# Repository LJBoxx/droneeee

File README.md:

# RP2350 Flight controller stack 

This repo contains the design files for a rp2350 based flight controller stack, with an [am32](https://wiki.am32.ca/development/Hardware-Design.html) based 4-in-1 modulable esc.
The esc part is split onto 3 boards : 
- top and bottoma board with logic and mosfet drivers (logic)
- middle with mosfets and power converters (powerstage)

This design allows for repairability, if you want to change the power board for a higher current one or if you have burnt it, just swap it out and solder a new board ! 

I also wanted to experiment with the newly supported rp2350 mcu on betaflight ! Madflight has an esc but I haven't seen any on a 30.5x30.5 "classic" format yet.

Thhe flight controller is quite simple and only has support for the essential to fly digital fpv with : 
- uart for elrs/radio transceiver 
- uart for video like openipc or dji
- uart for gps (additionnal too!)
- one spare i2c port (because there was room for it :v)
- power (9v 3a max, 5v 3a max and 3v3 200ma max **only use if necessary**)

Additionally, there are also some betaflight rgb headers and buzzer. Since it is an rp2350 with PIO, it should be easy to repurpose the i2c port for something else. The pinout is also similar to the madflight fc3 but not exactly the same, in /src/firmware/betaflight/picoflight/config.h you will find the exact files needed to build a firmware along precompiled binary 

At first i wanted to make an esc to work with Alice's flight controller but in the end, i started changing some parts like power converters, removing analog parts and tried to overall optimize the design. In the end it wasnt the same anymore. I also wanted to experiment with the rp2350 as no flight controller exist yet with it. One more thing was trying to make even more compact designs than before, high density layout is fun but also a pain lol.. 

## Renders :

## Schematics 

# BOM 
| Name     | Qty     | Price  | Link   | Note |
| -------- | ------- | ------ | ------ | ----- |
| Components | 1     | 110usd  | /src/bom_export_fc.xls |
| PCB      | 3x5pcs  | 5usd/ea | https://jlcpcb.com/ | order each board design individually to have discounts !|
| total         |         | 125usd |  |shipping included

# ZINEE !!

# Build 
(to be done after i assemble it myself but basically soldering)

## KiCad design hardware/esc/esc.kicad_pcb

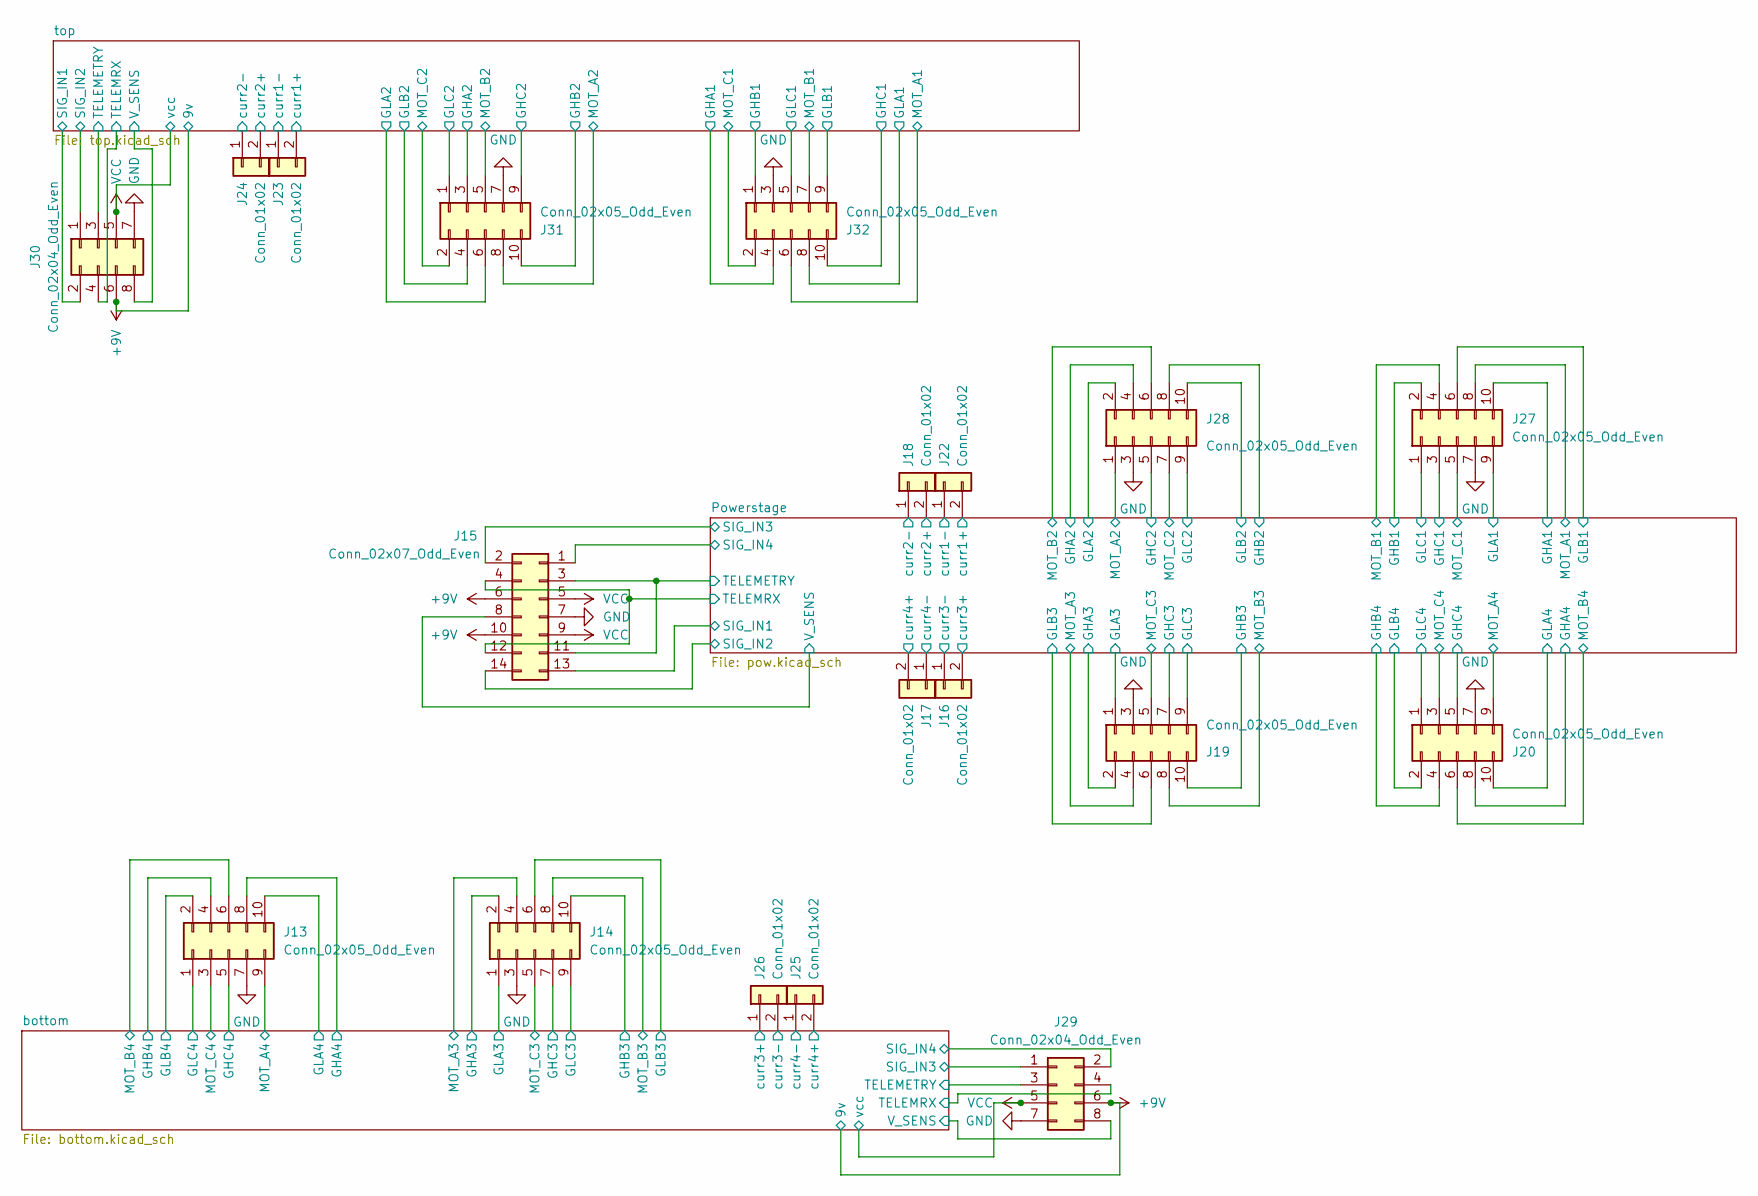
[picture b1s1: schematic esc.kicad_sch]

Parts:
J13, J14, J19, J20, J27, J28, J31, J32: Conn_02x05_Odd_Even; PinHeader_2x05_P1.00mm_Vertical; LCSC C22438182
J15: Conn_02x07_Odd_Even; PinHeader_2x07_P1.00mm_Vertical; LCSC x
J16, J17, J18, J22, J23, J24, J25, J26: Conn_01x02; PinHeader_1x02_P1.00mm_Vertical; LCSC C5138889
J29, J30: Conn_02x04_Odd_Even; PinHeader_2x04_P1.00mm_Vertical; LCSC x

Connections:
+9V: J15.6, J15.10, J29.6, J30.6; also elsewhere on the board
/Powerstage/GHA1: J27.10; also elsewhere on the board
/Powerstage/GHA2: J28.4; also elsewhere on the board
/Powerstage/GHA3: J19.2; also elsewhere on the board
/Powerstage/GHA4: J20.8; also elsewhere on the board
/Powerstage/GHB1: J27.2; also elsewhere on the board
/Powerstage/GHB2: J28.8; also elsewhere on the board
/Powerstage/GHB3: J19.10; also elsewhere on the board
/Powerstage/GHB4: J20.4; also elsewhere on the board
/Powerstage/GHC1: J27.3; also elsewhere on the board
/Powerstage/GHC2: J28.5; also elsewhere on the board
/Powerstage/GHC3: J19.7; also elsewhere on the board
/Powerstage/GHC4: J20.5; also elsewhere on the board
/Powerstage/GLA1: J27.9; also elsewhere on the board
/Powerstage/GLA2: J28.2; also elsewhere on the board
/Powerstage/GLA3: J19.1; also elsewhere on the board
/Powerstage/GLA4: J20.10; also elsewhere on the board
/Powerstage/GLB1: J27.6; also elsewhere on the board
/Powerstage/GLB2: J28.10; also elsewhere on the board
/Powerstage/GLB3: J19.6; also elsewhere on the board
/Powerstage/GLB4: J20.2; also elsewhere on the board
/Powerstage/GLC1: J27.1; also elsewhere on the board
/Powerstage/GLC2: J28.9; also elsewhere on the board
/Powerstage/GLC3: J19.9; also elsewhere on the board
/Powerstage/GLC4: J20.1; also elsewhere on the board
/Powerstage/MOT_A1: J27.8; also elsewhere on the board
/Powerstage/MOT_A2: J28.1; also elsewhere on the board
/Powerstage/MOT_A3: J19.4; also elsewhere on the board
/Powerstage/MOT_A4: J20.9; also elsewhere on the board
/Powerstage/MOT_B1: J27.4; also elsewhere on the board
/Powerstage/MOT_B2: J28.6; also elsewhere on the board
/Powerstage/MOT_B3: J19.8; also elsewhere on the board
/Powerstage/MOT_B4: J20.6; also elsewhere on the board
/Powerstage/MOT_C1: J27.5; also elsewhere on the board
/Powerstage/MOT_C2: J28.7; also elsewhere on the board
/Powerstage/MOT_C3: J19.5; also elsewhere on the board
/Powerstage/MOT_C4: J20.3; also elsewhere on the board
/Powerstage/SIG_IN1: J15.13; also elsewhere on the board
/Powerstage/SIG_IN2: J15.14; also elsewhere on the board
/Powerstage/SIG_IN3: J15.2; also elsewhere on the board
/Powerstage/SIG_IN4: J15.1; also elsewhere on the board
/Powerstage/TELEMETRY: J15.3, J15.11; also elsewhere on the board
/Powerstage/TELEMRX: J15.4, J15.12; also elsewhere on the board
/Powerstage/V_SENS: J15.8; also elsewhere on the board
/Powerstage/curr1+: J22.2; also elsewhere on the board
/Powerstage/curr1-: J22.1; also elsewhere on the board
/Powerstage/curr2+: J18.2; also elsewhere on the board
/Powerstage/curr2-: J18.1; also elsewhere on the board
/Powerstage/curr3+: J16.2; also elsewhere on the board
/Powerstage/curr3-: J16.1; also elsewhere on the board
/Powerstage/curr4+: J17.2; also elsewhere on the board
/Powerstage/curr4-: J17.1; also elsewhere on the board
/bottom/GHA3: J14.2; also elsewhere on the board
/bottom/GHA4: J13.8; also elsewhere on the board
/bottom/GHB3: J14.10; also elsewhere on the board
/bottom/GHB4: J13.4; also elsewhere on the board
/bottom/GHC3: J14.7; also elsewhere on the board
/bottom/GHC4: J13.5; also elsewhere on the board
/bottom/GLA3: J14.1; also elsewhere on the board
/bottom/GLA4: J13.10; also elsewhere on the board
/bottom/GLB3: J14.6; also elsewhere on the board
/bottom/GLB4: J13.2; also elsewhere on the board
/bottom/GLC3: J14.9; also elsewhere on the board
/bottom/GLC4: J13.1; also elsewhere on the board
/bottom/MOT_A3: J14.4; also elsewhere on the board
/bottom/MOT_A4: J13.9; also elsewhere on the board
/bottom/MOT_B3: J14.8; also elsewhere on the board
/bottom/MOT_B4: J13.6; also elsewhere on the board
/bottom/MOT_C3: J14.5; also elsewhere on the board
/bottom/MOT_C4: J13.3; also elsewhere on the board
/bottom/SIG_IN3: J29.1; also elsewhere on the board
/bottom/SIG_IN4: J29.2; also elsewhere on the board
/bottom/TELEMETRY: J29.3; also elsewhere on the board
/bottom/TELEMRX: J29.4; also elsewhere on the board
/bottom/V_SENS: J29.8; also elsewhere on the board
/bottom/curr3+: J26.1; also elsewhere on the board
/bottom/curr3-: J26.2; also elsewhere on the board
/bottom/curr4+: J25.2; also elsewhere on the board
/bottom/curr4-: J25.1; also elsewhere on the board
GND: J13.7, J14.3, J15.7, J19.3, J20.7, J27.7, J28.3, J29.7, J30.7, J31.7, J32.3; also elsewhere on the board
VCC: J15.5, J15.9, J29.5, J30.5; also elsewhere on the board

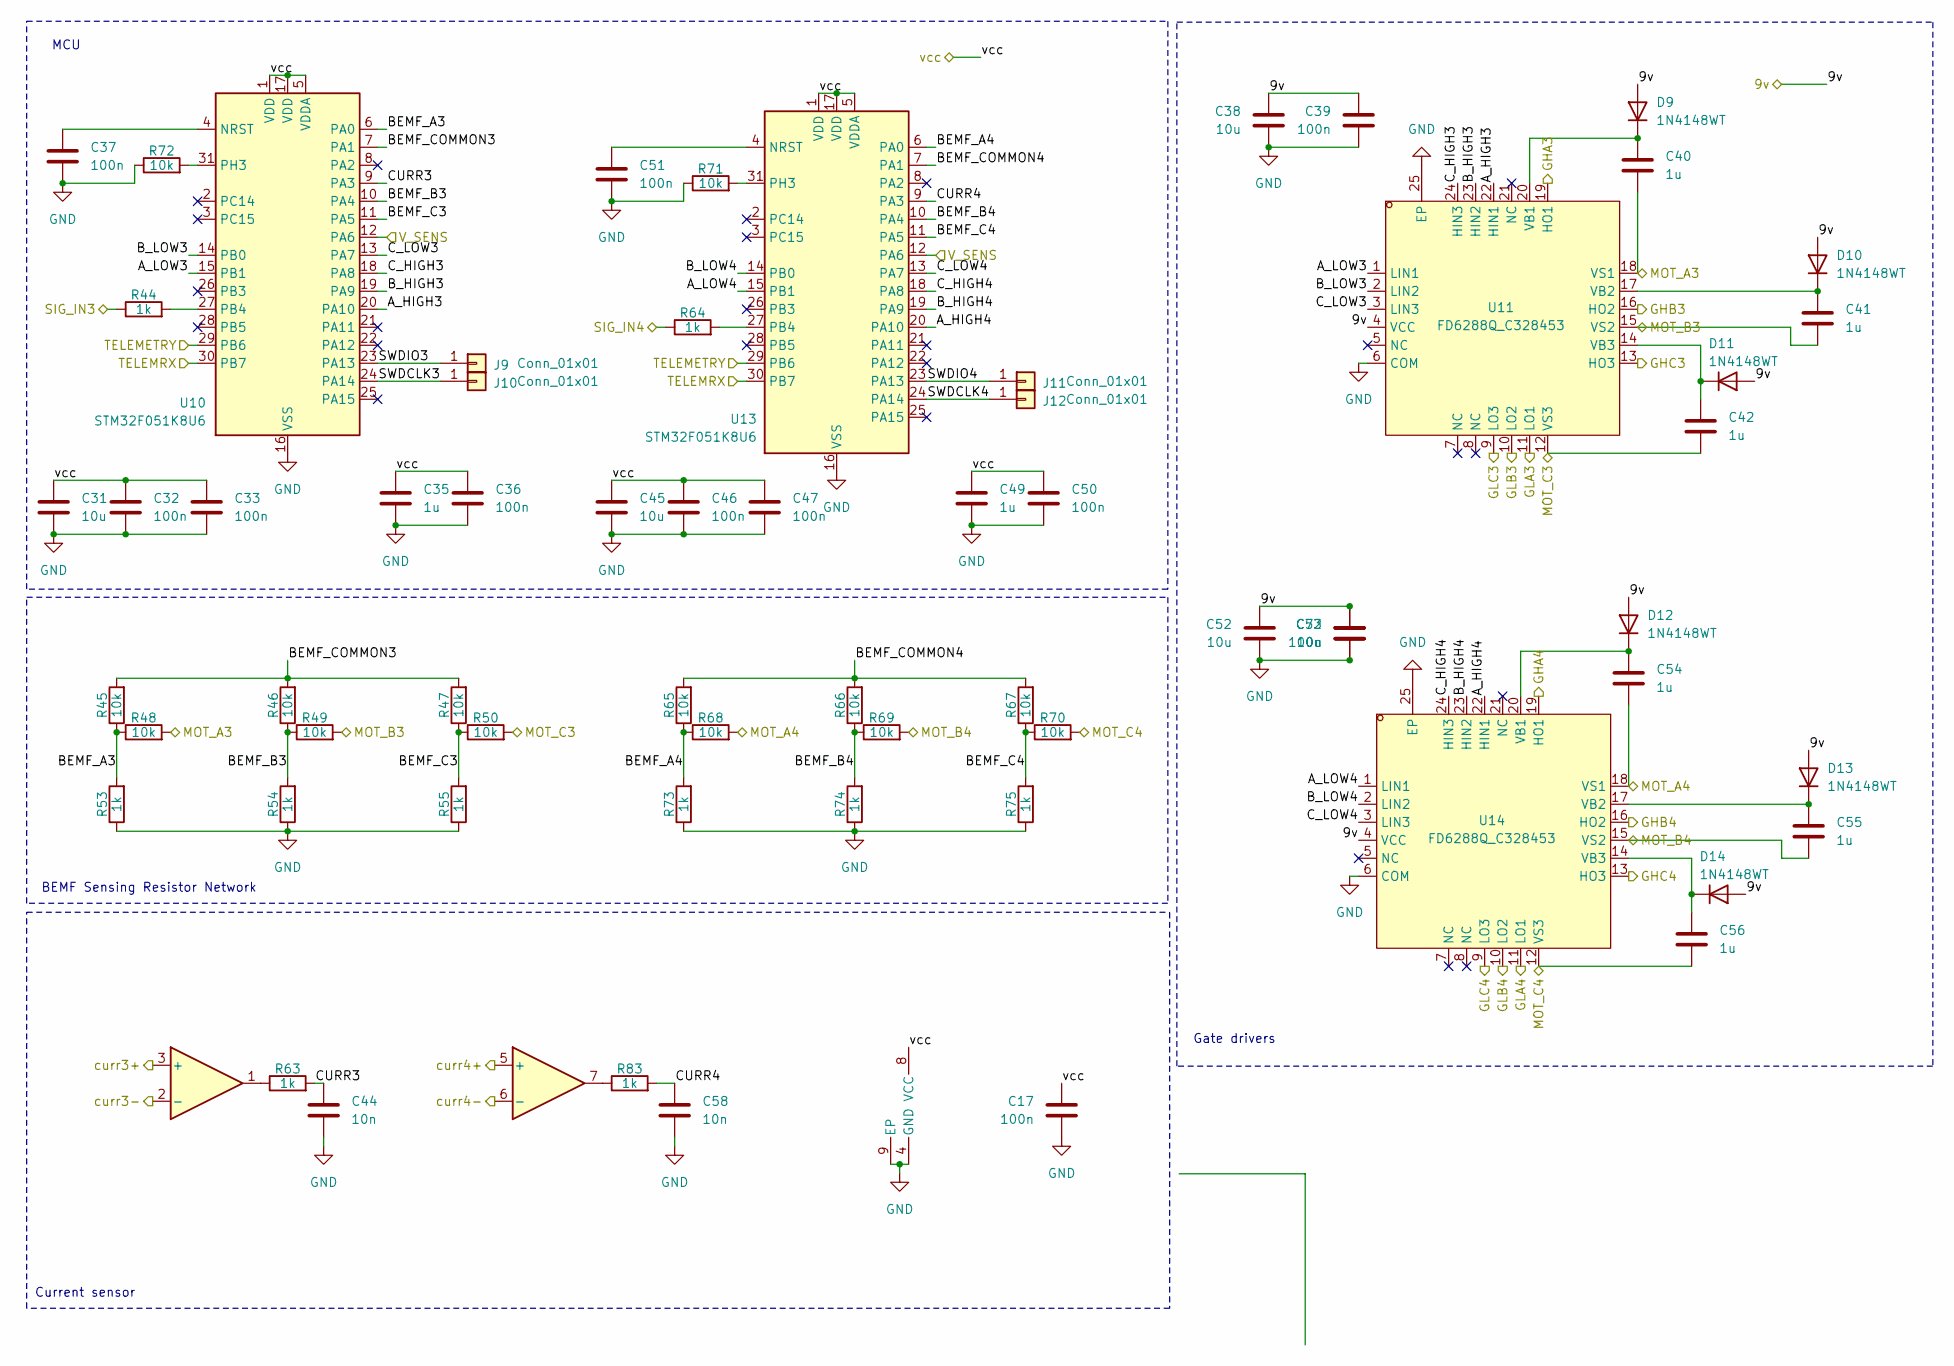
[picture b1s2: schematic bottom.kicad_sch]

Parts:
C17, C32, C33, C36, C37, C39, C46, C47, C50, C51, C53: 100n; C_0402_1005Metric; LCSC C1525
C31, C45: 10u; C_0805_2012Metric; LCSC C3039694
C35, C40, C41, C42, C49, C54, C55, C56: 1u; C_0603_1608Metric; LCSC C15849
C38, C52, C72: 10u; C_0603_1608Metric; LCSC C962136
C44, C58: 10n; C_0402_1005Metric; LCSC C15195
D9, D10, D11, D12, D13, D14: 1N4148WT; D_SOD-523; LCSC C917006
J9, J10, J11, J12: Conn_01x01; TestPoint_Pad_D1.0mm; LCSC x
R44, R53, R54, R55, R63, R64, R73, R74, R75, R83: 1k; R_0402_1005Metric; LCSC C445596
R45, R46, R47, R48, R49, R50, R65, R66, R67, R68, R69, R70, R71, R72: 10k; R_0402_1005Metric; LCSC C190095
U6: INA2180A1; WSON-8-1EP_2x2mm_P0.5mm_EP0.9x1.6mm; LCSC C2873353
U10, U13: STM32F051K8U6; QFN-32-1EP_5x5mm_P0.5mm_EP3.45x3.45mm; LCSC C72339
U11, U14: FD6288Q_C328453; QFN-24_L4.0-W4.0-P0.50-BL-EP2.6; LCSC Part C328453

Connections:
+9V: C38.1, C39.2, C52.1, C53.2, C72.1, D9.2 (A), D10.2 (A), D11.2 (A), D12.2 (A), D13.2 (A), D14.2 (A), U11.4 (VCC), U14.4 (VCC); also elsewhere on the board
/bottom/A_HIGH3: U10.20 (PA10), U11.22 (HIN1)
/bottom/A_HIGH4: U13.20 (PA10), U14.22 (HIN1)
/bottom/A_LOW3: U10.15 (PB1), U11.1 (LIN1)
/bottom/A_LOW4: U13.15 (PB1), U14.1 (LIN1)
/bottom/BEMF_A3: R45.1, R48.1, R53.2, U10.6 (PA0)
/bottom/BEMF_A4: R65.1, R68.1, R73.2, U13.6 (PA0)
/bottom/BEMF_B3: R46.1, R49.1, R54.2, U10.10 (PA4)
/bottom/BEMF_B4: R66.1, R69.1, R74.2, U13.10 (PA4)
/bottom/BEMF_C3: R47.1, R50.1, R55.2, U10.11 (PA5)
/bottom/BEMF_C4: R67.1, R70.1, R75.2, U13.11 (PA5)
/bottom/BEMF_COMMON3: R45.2, R46.2, R47.2, U10.7 (PA1)
/bottom/BEMF_COMMON4: R65.2, R66.2, R67.2, U13.7 (PA1)
/bottom/B_HIGH3: U10.19 (PA9), U11.23 (HIN2)
/bottom/B_HIGH4: U13.19 (PA9), U14.23 (HIN2)
/bottom/B_LOW3: U10.14 (PB0), U11.2 (LIN2)
/bottom/B_LOW4: U13.14 (PB0), U14.2 (LIN2)
/bottom/CURR3: C44.1, R63.2, U10.9 (PA3)
/bottom/CURR4: C58.1, R83.2, U13.9 (PA3)
/bottom/C_HIGH3: U10.18 (PA8), U11.24 (HIN3)
/bottom/C_HIGH4: U13.18 (PA8), U14.24 (HIN3)
/bottom/C_LOW3: U10.13 (PA7), U11.3 (LIN3)
/bottom/C_LOW4: U13.13 (PA7), U14.3 (LIN3)
/bottom/GHA3: U11.19 (HO1); also elsewhere on the board
/bottom/GHA4: U14.19 (HO1); also elsewhere on the board
/bottom/GHB3: U11.16 (HO2); also elsewhere on the board
/bottom/GHB4: U14.16 (HO2); also elsewhere on the board
/bottom/GHC3: U11.13 (HO3); also elsewhere on the board
/bottom/GHC4: U14.13 (HO3); also elsewhere on the board
/bottom/GLA3: U11.11 (LO1); also elsewhere on the board
/bottom/GLA4: U14.11 (LO1); also elsewhere on the board
/bottom/GLB3: U11.10 (LO2); also elsewhere on the board
/bottom/GLB4: U14.10 (LO2); also elsewhere on the board
/bottom/GLC3: U11.9 (LO3); also elsewhere on the board
/bottom/GLC4: U14.9 (LO3); also elsewhere on the board
/bottom/MOT_A3: C40.1, R48.2, U11.18 (VS1); also elsewhere on the board
/bottom/MOT_A4: C54.1, R68.2, U14.18 (VS1); also elsewhere on the board
/bottom/MOT_B3: C41.1, R49.2, U11.15 (VS2); also elsewhere on the board
/bottom/MOT_B4: C55.1, R69.2, U14.15 (VS2); also elsewhere on the board
/bottom/MOT_C3: C42.1, R50.2, U11.12 (VS3); also elsewhere on the board
/bottom/MOT_C4: C56.1, R70.2, U14.12 (VS3); also elsewhere on the board
/bottom/SIG_IN3: R44.1; also elsewhere on the board
/bottom/SIG_IN4: R64.1; also elsewhere on the board
/bottom/SWDCLK3: J10.1 (Pin_1_1), U10.24 (PA14)
/bottom/SWDCLK4: J12.1 (Pin_1_1), U13.24 (PA14)
/bottom/SWDIO3: J9.1 (Pin_1_1), U10.23 (PA13)
/bottom/SWDIO4: J11.1 (Pin_1_1), U13.23 (PA13)
/bottom/TELEMETRY: U10.29 (PB6), U13.29 (PB6); also elsewhere on the board
/bottom/TELEMRX: U10.30 (PB7), U13.30 (PB7); also elsewhere on the board
/bottom/V_SENS: U10.12 (PA6), U13.12 (PA6); also elsewhere on the board
/bottom/curr3+: U6.3 (+); also elsewhere on the board
/bottom/curr3-: U6.2 (-); also elsewhere on the board
/bottom/curr4+: U6.5 (+); also elsewhere on the board
/bottom/curr4-: U6.6 (-); also elsewhere on the board
GND: C17.2, C31.2, C32.2, C33.2, C35.2, C36.2, C37.2, C38.2, C39.1, C44.2, C45.2, C46.2, C47.2, C49.2, C50.2, C51.2, C52.2, C53.1, C58.2, C72.2, R53.1, R54.1, R55.1, R71.1, R72.1, R73.1, R74.1, R75.1, U6.4 (GND), U6.9 (EP), U10.16 (VSS), U10.32 (VSS), U10.33 (VSS), U11.6 (COM), U11.25 (EP), U13.16 (VSS), U13.32 (VSS), U13.33 (VSS), U14.6 (COM), U14.25 (EP); also elsewhere on the board
unnamed: C40.2, D9.1 (K), U11.20 (VB1)
unnamed: C41.2, D10.1 (K), U11.17 (VB2)
unnamed: C42.2, D11.1 (K), U11.14 (VB3)
unnamed: C54.2, D12.1 (K), U14.20 (VB1)
unnamed: C55.2, D13.1 (K), U14.17 (VB2)
unnamed: C56.2, D14.1 (K), U14.14 (VB3)
unnamed: R63.1, U6.1
unnamed: R83.1, U6.7
unnamed: C37.1, U10.4 (NRST)
unnamed: R44.2, U10.27 (PB4)
unnamed: R72.2, U10.31 (PH3)
unnamed: C51.1, U13.4 (NRST)
unnamed: R64.2, U13.27 (PB4)
unnamed: R71.2, U13.31 (PH3)
VCC: C17.1, C31.1, C32.1, C33.1, C35.1, C36.1, C45.1, C46.1, C47.1, C49.1, C50.1, U6.8 (VCC), U10.1 (VDD), U10.5 (VDDA), U10.17 (VDD), U13.1 (VDD), U13.5 (VDDA), U13.17 (VDD); also elsewhere on the board

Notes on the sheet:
Current sensor
BEMF Sensing Resistor Network
Gate drivers
MCU

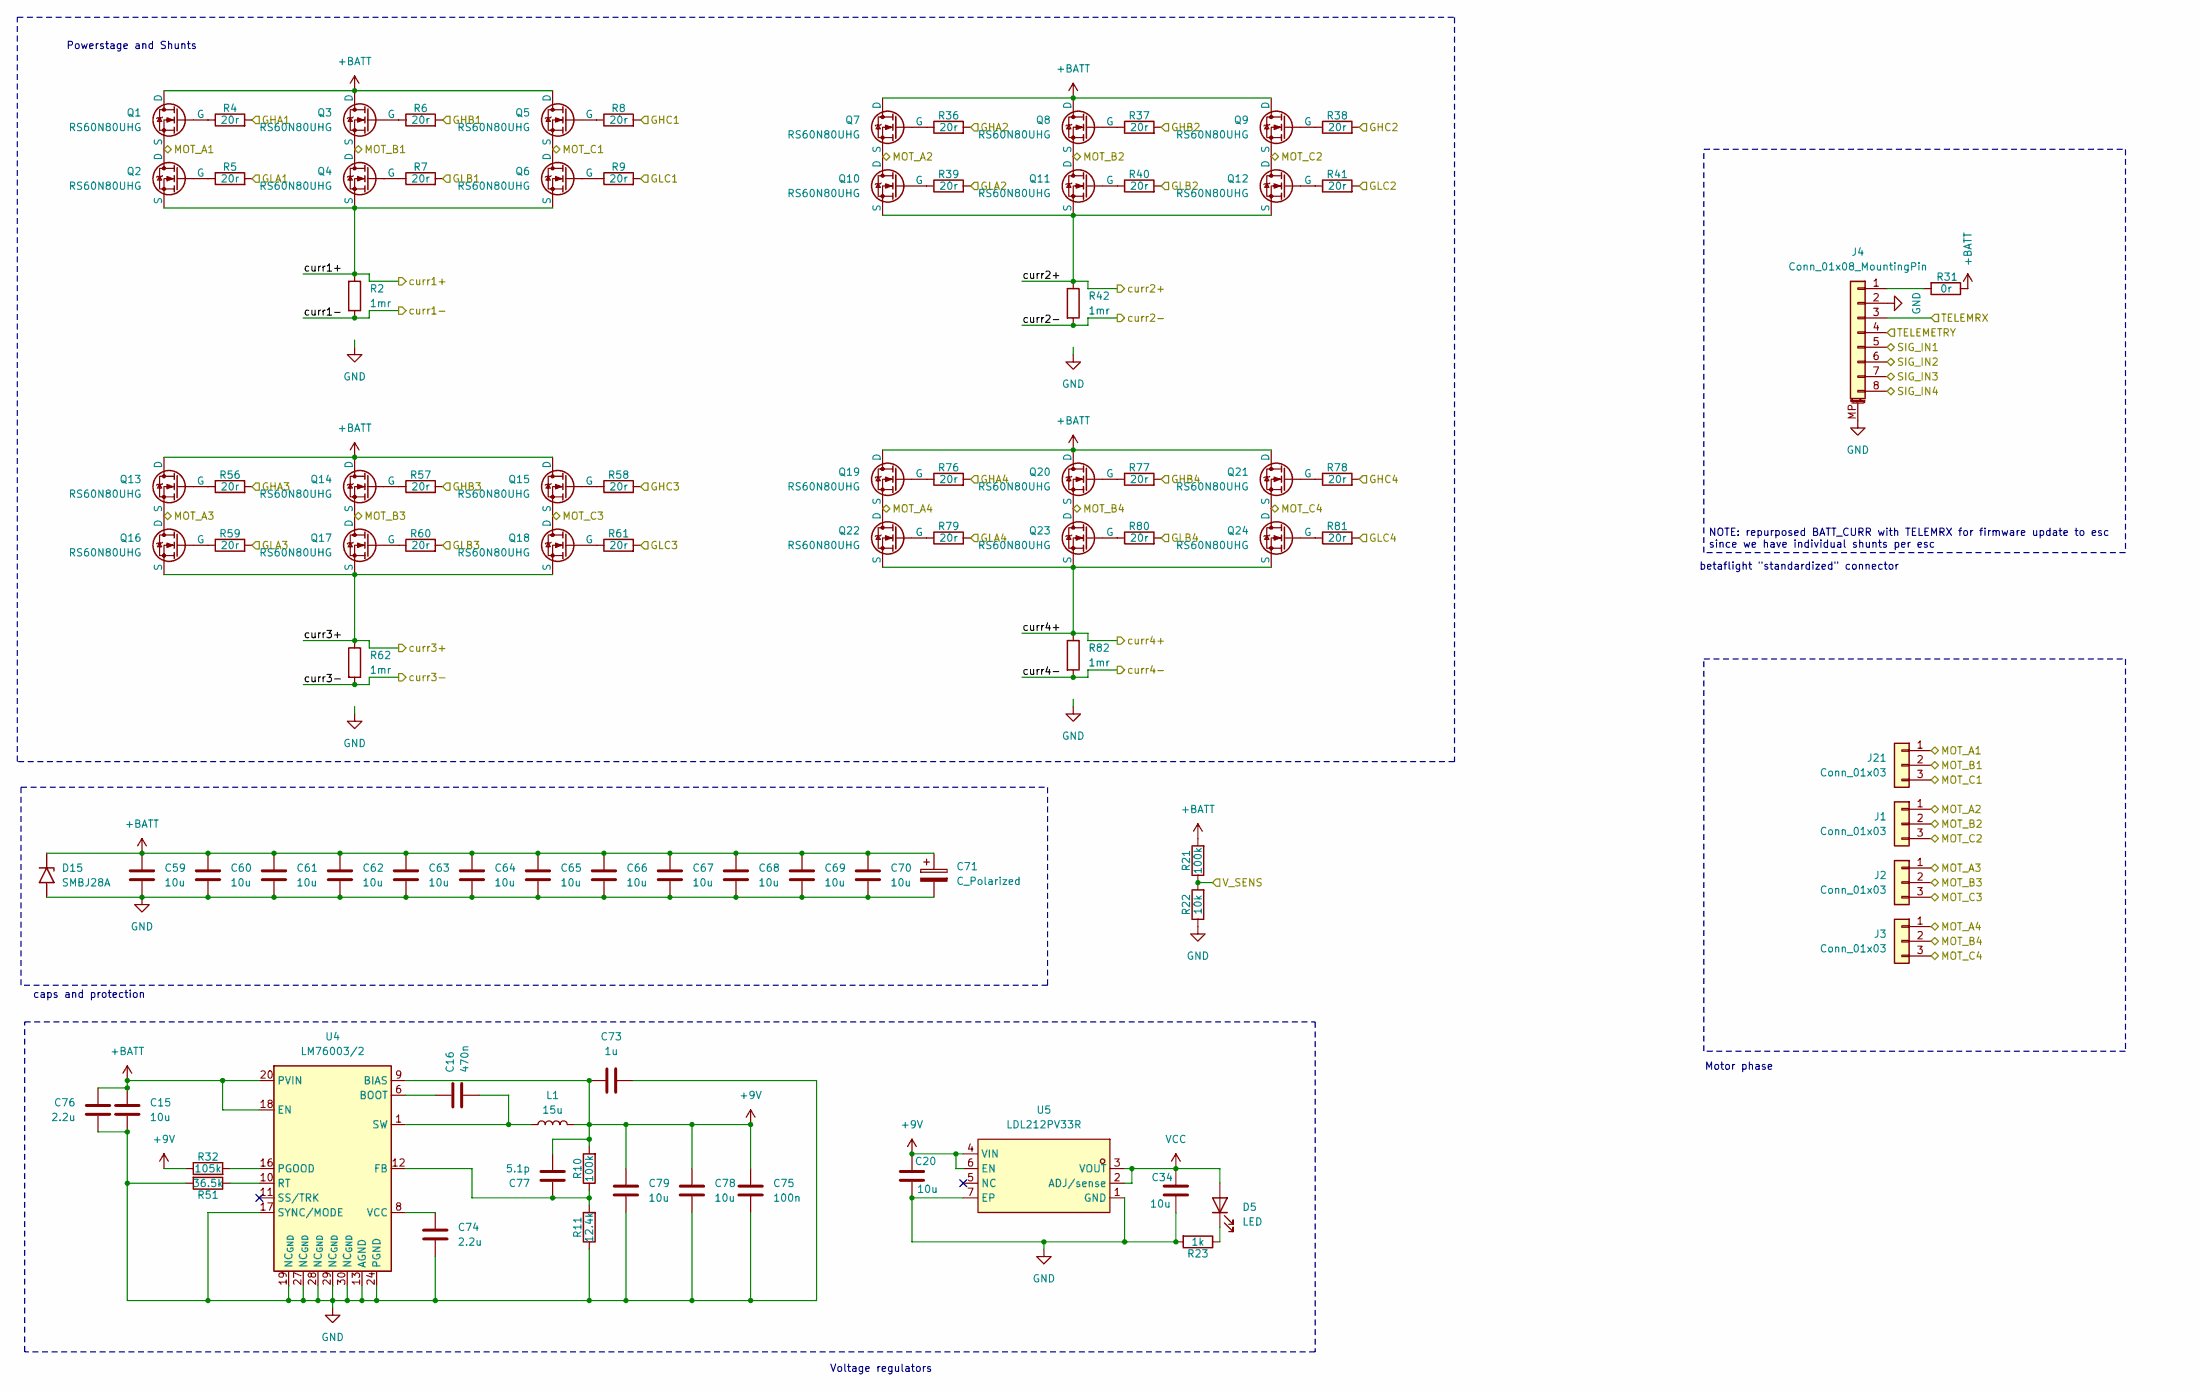
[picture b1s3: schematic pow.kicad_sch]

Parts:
C15, C20, C34, C59, C60, C61, C62, C63, C64, C65, C66, C67, C68, C69, C70, C78, C79: 10u; C_0805_2012Metric; LCSC C3039694
C16: 470n; C_0402_1005Metric; LCSC C92361
C71: C_Polarized; C_Disc_D5.0mm_W2.5mm_P5.00mm; LCSC x
C73: 1u; C_0402_1005Metric; LCSC C913556
C74: 2.2u; C_0402_1005Metric; LCSC C12530
C75: 100n; C_0402_1005Metric; LCSC C1525
C76: 2.2u; C_0603_1608Metric; LCSC C913904
C77: 5.1p; C_0402_1005Metric; LCSC C541354
D5: LED; D_0603_1608Metric; LCSC C7496819
D15: SMBJ28A; D_SMB; LCSC C178227
J1, J2, J3, J21: Conn_01x03; Phase_Pads; LCSC x
J4: Conn_01x08_MountingPin; JST_SH_SM08B-SRSS-TB_1x08-1MP_P1.00mm_Horizontal; LCSC Part C160407
L1: 15u; inductor FANGCHENG FC-ALX 5050D-150MT; LCSC C5370912
Q1, Q2, Q3, Q4, Q5, Q6, Q7, Q8, Q9, Q10, Q11, Q12, Q13, Q14, Q15, Q16, Q17, Q18, Q19, Q20, Q21, Q22, Q23, Q24: RS60N80UHG; DFN-8_L5.8-W4.9-P1.27-LS6.0-BL-1; LCSC C51904706
R2, R42, R62, R82: 1mr; R_1210_3225Metric; LCSC C4173351
R4, R5, R6, R7, R8, R9, R36, R37, R38, R39, R40, R41, R56, R57, R58, R59, R60, R61, R76, R77, R78, R79, R80, R81: 20r; R_0402_1005Metric; LCSC C2909334
R10, R21: 100k; R_0402_1005Metric; LCSC C445619
R11: 12.4k; R_0402_1005Metric; LCSC C490814
R22: 10k; R_0402_1005Metric; LCSC C190095
R23: 1k; R_0402_1005Metric; LCSC C445596
R31: 0r; R_0402_1005Metric; LCSC x(shunt)
R32: 105k; R_0402_1005Metric; LCSC C2933067
R51: 36.5k; R_0402_1005Metric; LCSC C42396638
U4: LM76003/2; Texas_RNP0030B_WQFN-30-1EP_4x6mm_P0.5mm_EP1.8x4.5mm_Thermal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; LCSC C470958
U5: LDL212PV33R; DFN-6_L2.0-W2.0-P0.50-BL-EP1.45; MPN LDL212PV33R; LCSC Part C2969892

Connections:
+9V: C20.1, C73.1, C75.1, C77.2, C78.1, C79.1, L1.2, R10.2, R32.1, U4.9 (BIAS), U5.4 (VIN), U5.6 (EN); also elsewhere on the board
+BATT: C15.1, C59.1, C60.1, C61.1, C62.1, C63.1, C64.1, C65.1, C66.1, C67.1, C68.1, C69.1, C70.1, C71.1, C76.1, D15.1 (A1), Q1.D, Q3.D, Q5.D, Q7.D, Q8.D, Q9.D, Q13.D, Q14.D, Q15.D, Q19.D, Q20.D, Q21.D, R21.2, R31.1, U4.18 (EN), U4.20 (PVIN), U4.21 (PVIN), U4.22 (PVIN)
/Powerstage/GHA1: R4.2; also elsewhere on the board
/Powerstage/GHA2: R36.2; also elsewhere on the board
/Powerstage/GHA3: R56.2; also elsewhere on the board
/Powerstage/GHA4: R76.2; also elsewhere on the board
/Powerstage/GHB1: R6.2; also elsewhere on the board
/Powerstage/GHB2: R37.2; also elsewhere on the board
/Powerstage/GHB3: R57.2; also elsewhere on the board
/Powerstage/GHB4: R77.2; also elsewhere on the board
/Powerstage/GHC1: R8.2; also elsewhere on the board
/Powerstage/GHC2: R38.2; also elsewhere on the board
/Powerstage/GHC3: R58.2; also elsewhere on the board
/Powerstage/GHC4: R78.2; also elsewhere on the board
/Powerstage/GLA1: R5.2; also elsewhere on the board
/Powerstage/GLA2: R39.2; also elsewhere on the board
/Powerstage/GLA3: R59.2; also elsewhere on the board
/Powerstage/GLA4: R79.2; also elsewhere on the board
/Powerstage/GLB1: R7.2; also elsewhere on the board
/Powerstage/GLB2: R40.2; also elsewhere on the board
/Powerstage/GLB3: R60.2; also elsewhere on the board
/Powerstage/GLB4: R80.2; also elsewhere on the board
/Powerstage/GLC1: R9.2; also elsewhere on the board
/Powerstage/GLC2: R41.2; also elsewhere on the board
/Powerstage/GLC3: R61.2; also elsewhere on the board
/Powerstage/GLC4: R81.2; also elsewhere on the board
/Powerstage/MOT_A1: J21.1, Q1.S, Q2.D; also elsewhere on the board
/Powerstage/MOT_A2: J1.1, Q7.S, Q10.D; also elsewhere on the board
/Powerstage/MOT_A3: J2.1, Q13.S, Q16.D; also elsewhere on the board
/Powerstage/MOT_A4: J3.1, Q19.S, Q22.D; also elsewhere on the board
/Powerstage/MOT_B1: J21.2, Q3.S, Q4.D; also elsewhere on the board
/Powerstage/MOT_B2: J1.2, Q8.S, Q11.D; also elsewhere on the board
/Powerstage/MOT_B3: J2.2, Q14.S, Q17.D; also elsewhere on the board
/Powerstage/MOT_B4: J3.2, Q20.S, Q23.D; also elsewhere on the board
/Powerstage/MOT_C1: J21.3, Q5.S, Q6.D; also elsewhere on the board
/Powerstage/MOT_C2: J1.3, Q9.S, Q12.D; also elsewhere on the board
/Powerstage/MOT_C3: J2.3, Q15.S, Q18.D; also elsewhere on the board
/Powerstage/MOT_C4: J3.3, Q21.S, Q24.D; also elsewhere on the board
/Powerstage/SIG_IN1: J4.5; also elsewhere on the board
/Powerstage/SIG_IN2: J4.6; also elsewhere on the board
/Powerstage/SIG_IN3: J4.7; also elsewhere on the board
/Powerstage/SIG_IN4: J4.8; also elsewhere on the board
/Powerstage/TELEMETRY: J4.4; also elsewhere on the board
/Powerstage/TELEMRX: J4.3; also elsewhere on the board
/Powerstage/V_SENS: R21.1, R22.2; also elsewhere on the board
/Powerstage/curr1+: Q2.S, Q4.S, Q6.S, R2.1; also elsewhere on the board
/Powerstage/curr1-: R2.2; also elsewhere on the board
/Powerstage/curr2+: Q10.S, Q11.S, Q12.S, R42.1; also elsewhere on the board
/Powerstage/curr2-: R42.2; also elsewhere on the board
/Powerstage/curr3+: Q16.S, Q17.S, Q18.S, R62.1; also elsewhere on the board
/Powerstage/curr3-: R62.2; also elsewhere on the board
/Powerstage/curr4+: Q22.S, Q23.S, Q24.S, R82.1; also elsewhere on the board
/Powerstage/curr4-: R82.2; also elsewhere on the board
GND: C15.2, C20.2, C34.2, C59.2, C60.2, C61.2, C62.2, C63.2, C64.2, C65.2, C66.2, C67.2, C68.2, C69.2, C70.2, C71.2, C73.2, C74.2, C75.2, C76.2, C78.2, C79.2, D15.2 (A2), J4.2, J4.MP (MountPin), R11.1, R22.1, R23.2, R51.2, U4.13 (AGND), U4.14 (AGND), U4.15 (AGND), U4.17 (SYNC/MODE), U4.19 (NC_{GND}), U4.24 (PGND), U4.25 (PGND), U4.26 (PGND), U4.27 (NC_{GND}), U4.28 (NC_{GND}), U4.29 (NC_{GND}), U4.30 (NC_{GND}), U4.31 (AGND), U5.1 (GND), U5.7 (EP); also elsewhere on the board
unnamed: C16.2, L1.1, U4.1 (SW), U4.2 (SW), U4.3 (SW), U4.4 (SW), U4.5 (SW)
unnamed: D5.1 (K), R23.1
unnamed: J4.1, R31.2
unnamed: Q1.G, R4.1
unnamed: Q2.G, R5.1
unnamed: Q3.G, R6.1
unnamed: Q4.G, R7.1
unnamed: Q5.G, R8.1
unnamed: Q6.G, R9.1
unnamed: Q7.G, R36.1
unnamed: Q8.G, R37.1
unnamed: Q9.G, R38.1
unnamed: Q10.G, R39.1
unnamed: Q11.G, R40.1
unnamed: Q12.G, R41.1
unnamed: Q13.G, R56.1
unnamed: Q14.G, R57.1
unnamed: Q15.G, R58.1
unnamed: Q16.G, R59.1
unnamed: Q17.G, R60.1
unnamed: Q18.G, R61.1
unnamed: Q19.G, R76.1
unnamed: Q20.G, R77.1
unnamed: Q21.G, R78.1
unnamed: Q22.G, R79.1
unnamed: Q23.G, R80.1
unnamed: Q24.G, R81.1
unnamed: C16.1, U4.6 (BOOT)
unnamed: C77.1, R10.1, R11.2, U4.12 (FB)
unnamed: R32.2, U4.16 (PGOOD)
unnamed: R51.1, U4.10 (RT)
unnamed: C74.1, U4.8 (VCC)
VCC: C34.1, D5.2 (A), U5.2 (ADJ/sense), U5.3 (VOUT); also elsewhere on the board

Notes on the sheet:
NOTE: repurposed BATT_CURR with TELEMRX for firmware update to esc since we have individual shunts per esc
caps and protection
Powerstage and Shunts
betaflight "standardized" connector
Voltage regulators
Motor phase

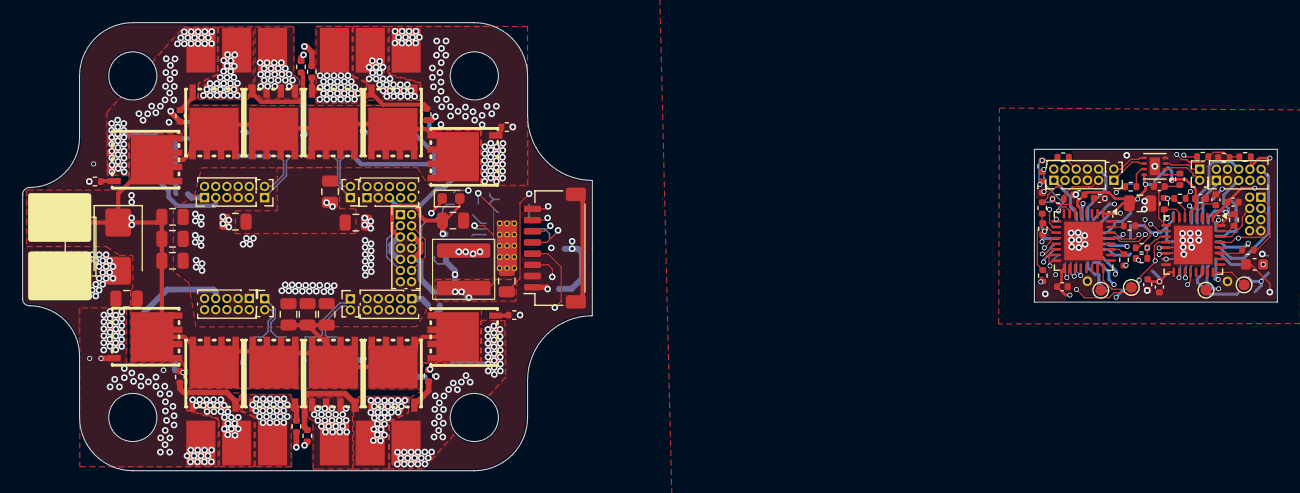
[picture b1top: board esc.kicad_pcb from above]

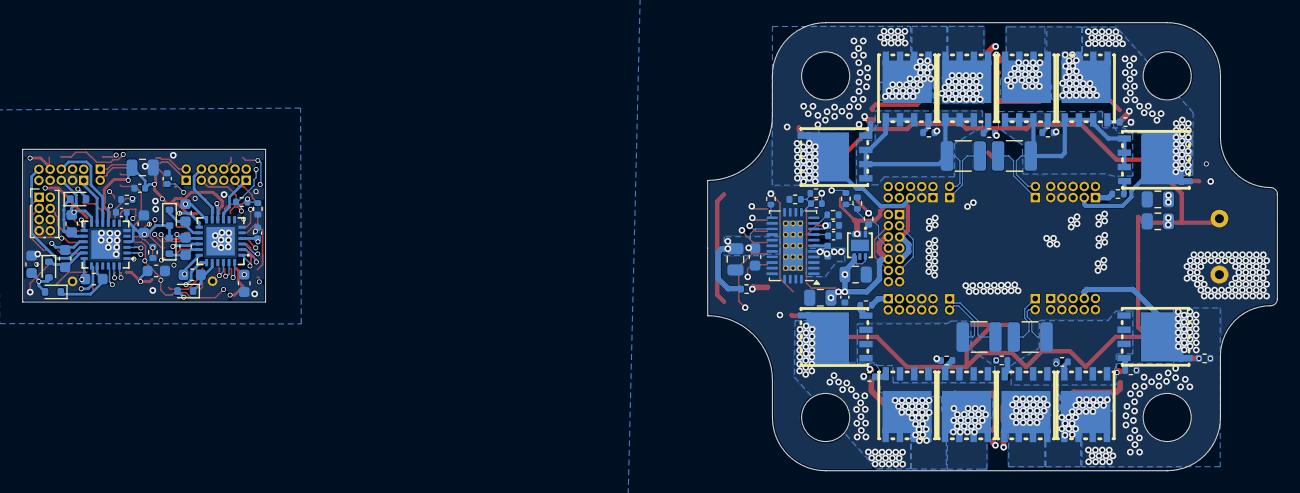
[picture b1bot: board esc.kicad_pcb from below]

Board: 6 copper layers, 112.0 x 40.0 mm, 173 parts (78 on the bottom side), 154 nets.
